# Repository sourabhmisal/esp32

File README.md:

# Custom ESP32 Microcontroller Development board

* Contains ESP32 Kicad schematic
* Anyone using this repository or schematic is open to use the schematic and develop a custom PCB for personal or commercial use. Do give initial credits and send a pull request to update your changes to the schematic or PCB. It would be helpful for all of us to develop the PCBs and, learn and improve our skills in this tough times. Cheers!

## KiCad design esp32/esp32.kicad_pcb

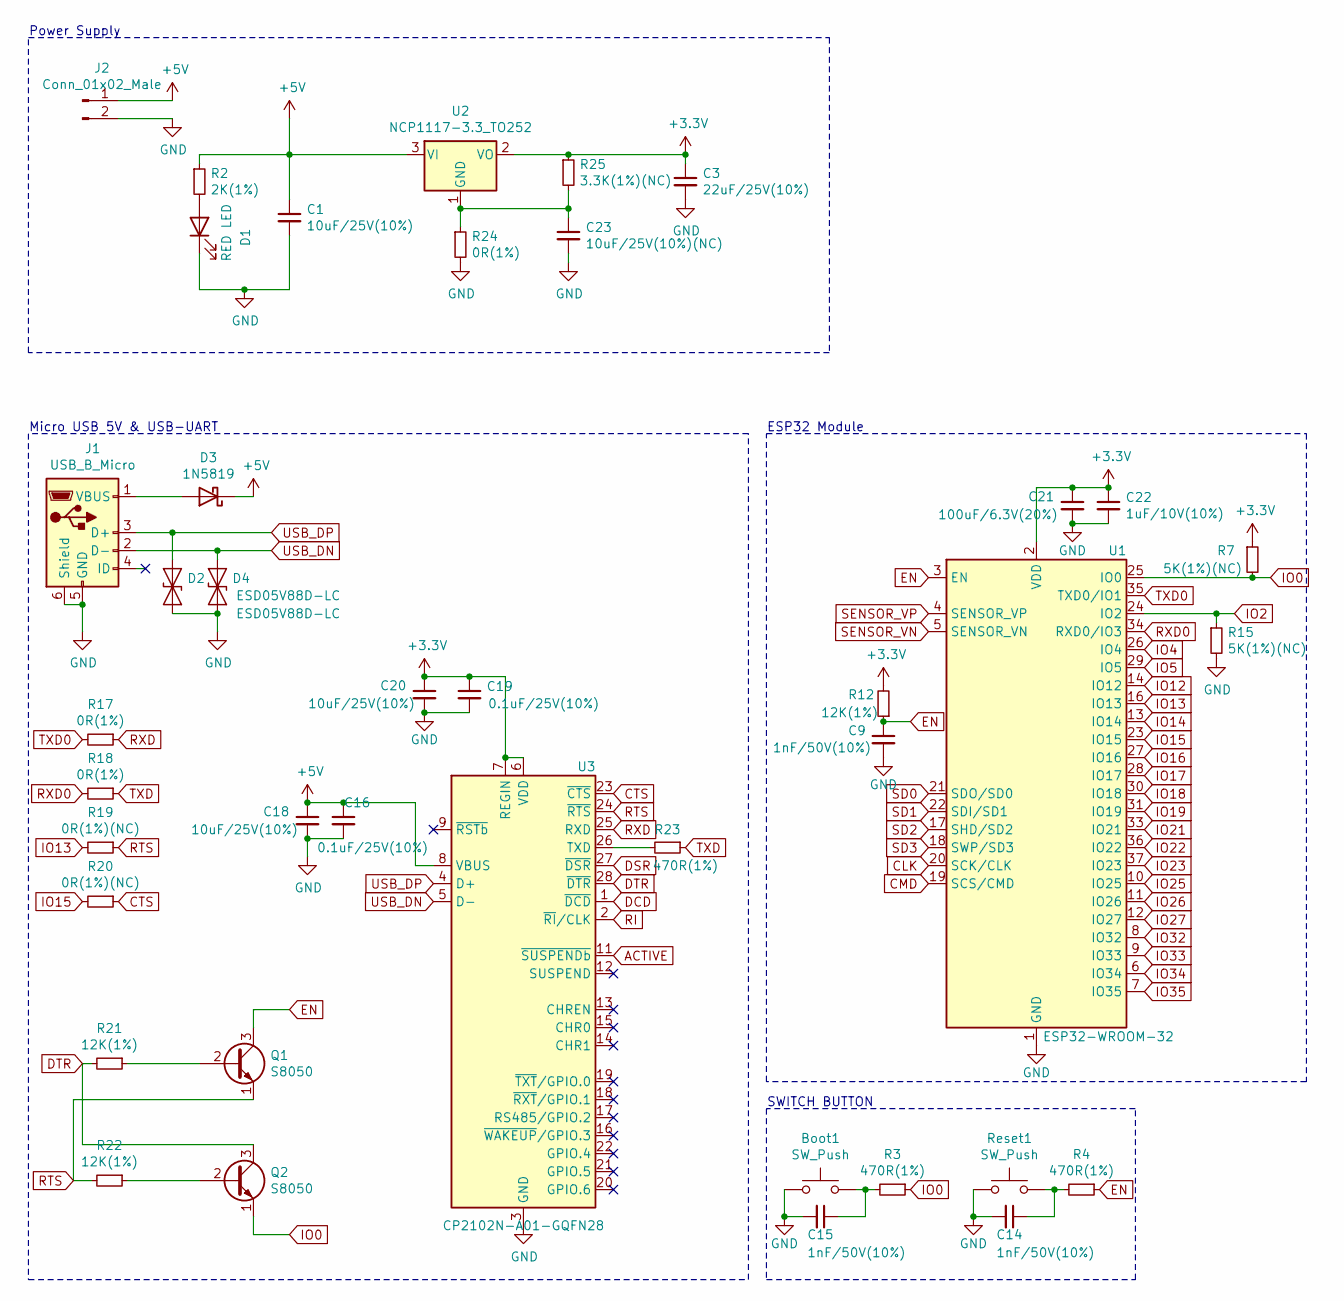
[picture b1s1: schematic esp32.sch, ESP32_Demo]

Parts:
Boot1: SW_Push; SW_Push_SPST_NO_Alps_SKRK
C1, C18, C20: 10uF/25V(10%); C_0603_1608Metric
C3: 22uF/25V(10%); C_0603_1608Metric
C9, C14, C15: 1nF/50V(10%); C_0402_1005Metric
C16, C19: 0.1uF/25V(10%); C_0402_1005Metric
C21: 100uF/6.3V(20%); C_0603_1608Metric
C22: 1uF/10V(10%); C_0402_1005Metric
C23: 10uF/25V(10%)(NC); C_0402_1005Metric
D1: RED LED; LED_0603_1608Metric
D2, D4: ESD05V88D-LC; D_0402_1005Metric
D3: 1N5819; D_0402_1005Metric
J1: USB_B_Micro; USB_Micro-B_Molex_47346-0001
J2: Conn_01x02_Male; JST_EH_B2B-EH-A_1x02_P2.50mm_Vertical
Q1, Q2: S8050; SOT-23
R2: 2K(1%); R_0402_1005Metric
R3, R4: 470R(1%); R_0402_1005Metric
R7, R15: 5K(1%)(NC); R_0402_1005Metric
R12, R21, R22: 12K(1%); R_0402_1005Metric
R17, R18, R24: 0R(1%); R_0402_1005Metric
R19, R20: 0R(1%)(NC); R_0402_1005Metric
R23: 470R(1%); C_0402_1005Metric
R25: 3.3K(1%)(NC); R_0402_1005Metric
Reset1: SW_Push; SW_Push_SPST_NO_Alps_SKRK
U1: ESP32-WROOM-32
U2: NCP1117-3.3_TO252; SOT-223
U3: CP2102N-A01-GQFN28; QFN-28-1EP_5x5mm_P0.5mm_EP3.35x3.35mm

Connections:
+3V3: C3.1, C19.1, C20.1, C21.1, C22.1, R7.1, R12.2, R25.1, U1.2 (VDD), U2.2 (VO), U3.6 (VDD), U3.7 (REGIN)
+5V: C1.1, C16.1, C18.1, D3.1 (K), J2.1, R2.1, U2.3 (VI), U3.8 (VBUS)
ACTIVE: U3.11 (~SUSPENDb)
CLK: U1.20 (SCK/CLK)
CMD: U1.19 (SCS/CMD)
CTS: R20.1, U3.23 (~CTS)
DCD: U3.1 (~DCD)
DSR: U3.27 (~DSR)
DTR: Q2.3 (C), R21.2, U3.28 (~DTR)
EN: C9.1, Q1.3 (C), R4.1, R12.1, U1.3 (EN)
GND: Boot1.1, C1.2, C3.2, C9.2, C14.2, C15.2, C16.2, C18.2, C19.2, C20.2, C21.2, C22.2, C23.2, D1.1 (K), D2.2 (A2), D4.2 (A2), J1.5 (GND), J1.6 (Shield), J2.2, R15.2, R24.2, Reset1.1, U1.1 (GND), U1.15 (GND), U1.38 (GND), U1.39 (GND), U3.3 (GND), U3.29 (GND)
IO0: Q2.1 (E), R3.1, R7.2, U1.25 (IO0)
IO2: R15.1, U1.24 (IO2)
IO4: U1.26 (IO4)
IO5: U1.29 (IO5)
IO12: U1.14 (IO12)
IO13: R19.2, U1.16 (IO13)
IO14: U1.13 (IO14)
IO15: R20.2, U1.23 (IO15)
IO16: U1.27 (IO16)
IO17: U1.28 (IO17)
IO18: U1.30 (IO18)
IO19: U1.31 (IO19)
IO21: U1.33 (IO21)
IO22: U1.36 (IO22)
IO23: U1.37 (IO23)
IO25: U1.10 (IO25)
IO26: U1.11 (IO26)
IO27: U1.12 (IO27)
IO32: U1.8 (IO32)
IO33: U1.9 (IO33)
IO34: U1.6 (IO34)
IO35: U1.7 (IO35)
unnamed: Boot1.2, C15.1, R3.2
unnamed: C14.1, R4.2, Reset1.2
unnamed: C23.1, R24.1, R25.2, U2.1 (GND)
unnamed: D1.2 (A), R2.2
unnamed: D3.2 (A), J1.1 (VBUS)
unnamed: Q1.2 (B), R21.1
unnamed: Q2.2 (B), R22.1
unnamed: R23.2, U3.26 (TXD)
RI: U3.2 (~RI~/CLK)
RTS: Q1.1 (E), R19.1, R22.2, U3.24 (~RTS)
RXD: R17.1, U3.25 (RXD)
RXD0: R18.2, U1.34 (RXD0/IO3)
SD0: U1.21 (SDO/SD0)
SD1: U1.22 (SDI/SD1)
SD2: U1.17 (SHD/SD2)
SD3: U1.18 (SWP/SD3)
SENSOR_VN: U1.5 (SENSOR_VN)
SENSOR_VP: U1.4 (SENSOR_VP)
TXD: R18.1, R23.1
TXD0: R17.2, U1.35 (TXD0/IO1)
USB_DN: D4.1 (A1), J1.2 (D-), U3.5 (D-)
USB_DP: D2.1 (A1), J1.3 (D+), U3.4 (D+)

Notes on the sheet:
Power Supply
Micro USB 5V & USB-UART
SWITCH BUTTON
ESP32 Module

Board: 4 copper layers, 40 parts (0 on the bottom side), 25 nets, no tracks yet.

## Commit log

2020-10-07 Initial Repository
